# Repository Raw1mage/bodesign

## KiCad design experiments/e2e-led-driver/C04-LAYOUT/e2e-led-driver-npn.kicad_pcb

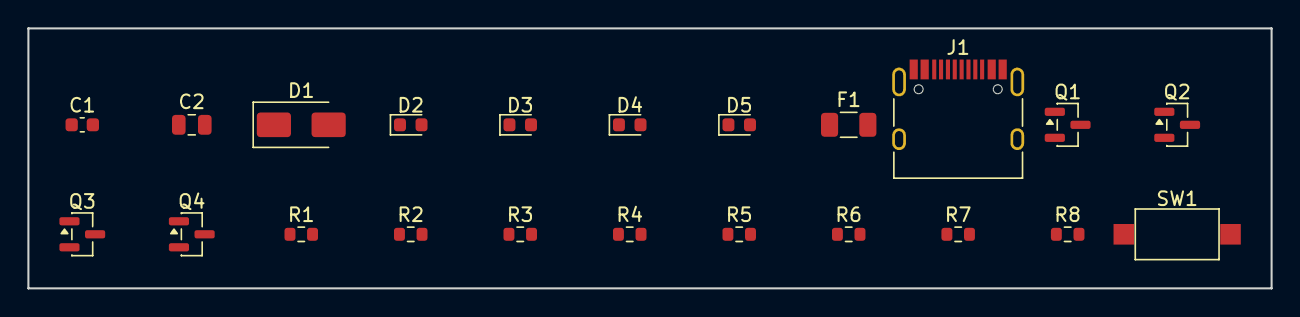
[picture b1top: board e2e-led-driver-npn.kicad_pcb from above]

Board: 2 copper layers, 90.8 x 19.0 mm, 22 parts (0 on the bottom side), 15 nets, no tracks yet.

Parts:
C1: C_0603_1608Metric
C2: C_0805_2012Metric
D1: D_SMA
D2, D3, D4, D5: LED_0603_1608Metric
F1: Fuse_1206_3216Metric
J1: USB_C_Receptacle_HRO_TYPE-C-31-M-12
Q1, Q2, Q3, Q4: SOT-23
R1, R2, R3, R4, R5, R6, R7, R8: R_0603_1608Metric
SW1: SW_SPST_CK_RS282G05A3

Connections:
CC1: J1.A5, R1.1
CC2: J1.B5, R2.1
GND: C1.2, C2.2, D1.2, J1.A1, J1.A12, J1.B1, J1.B12, R1.2, R2.2, R3.2, R4.2, R5.2, R6.2, R8.2
LED1_C: D2.1, Q1.2
LED2_C: D3.1, Q2.2
LED3_C: D4.1, Q3.2
LED4_C: D5.1, Q4.2
Q1_E: Q1.3, R3.1
Q2_E: Q2.3, R4.1
Q3_E: Q3.3, R5.1
Q4_E: Q4.3, R6.1
VBIAS: Q1.1, Q2.1, Q3.1, Q4.1, R7.2, R8.1
VBUS: D1.1, F1.1, J1.A4, J1.A9, J1.B4, J1.B9
VBUS_F: F1.2, SW1.1
VBUS_SW: C1.1, C2.1, D2.2, D3.2, D4.2, D5.2, R7.1, SW1.2

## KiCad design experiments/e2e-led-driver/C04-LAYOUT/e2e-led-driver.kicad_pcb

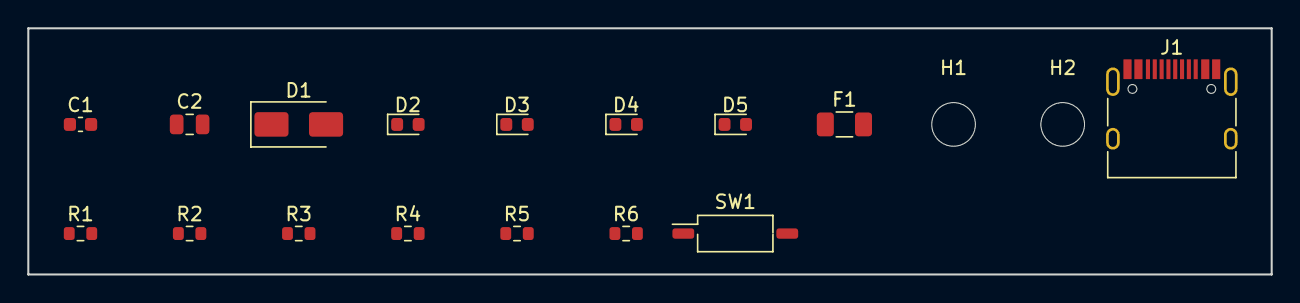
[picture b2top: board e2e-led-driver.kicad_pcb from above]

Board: 2 copper layers, 91.1 x 18.0 mm, 18 parts (0 on the bottom side), 10 nets, no tracks yet.

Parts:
C1: C_0603_1608Metric
C2: C_0805_2012Metric
D1: D_SMA
D2, D3, D4, D5: LED_0603_1608Metric
F1: Fuse_1206_3216Metric
H1, H2: MountingHole_3.2mm_M3
J1: USB_C_Receptacle_HRO_TYPE-C-31-M-12
R1, R2, R3, R4, R5, R6: R_0603_1608Metric
SW1: SW_DIP_SPSTx01_Slide_Copal_CHS-01B_W7.62mm_P1.27mm

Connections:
CC1: J1.A5, R1.1
CC2: J1.B5, R2.1
GND: C1.2, C2.2, D1.2, J1.A1, J1.A12, J1.B1, J1.B12, R1.2, R2.2, R3.2, R4.2, R5.2, R6.2
LED1_K: D2.1, R3.1
LED2_K: D3.1, R4.1
LED3_K: D4.1, R5.1
LED4_K: D5.1, R6.1
VBUS: D1.1, F1.1, J1.A4, J1.A9, J1.B4, J1.B9
VBUS_F: F1.2, SW1.1
VBUS_SW: C1.1, C2.1, D2.2, D3.2, D4.2, D5.2, SW1.2

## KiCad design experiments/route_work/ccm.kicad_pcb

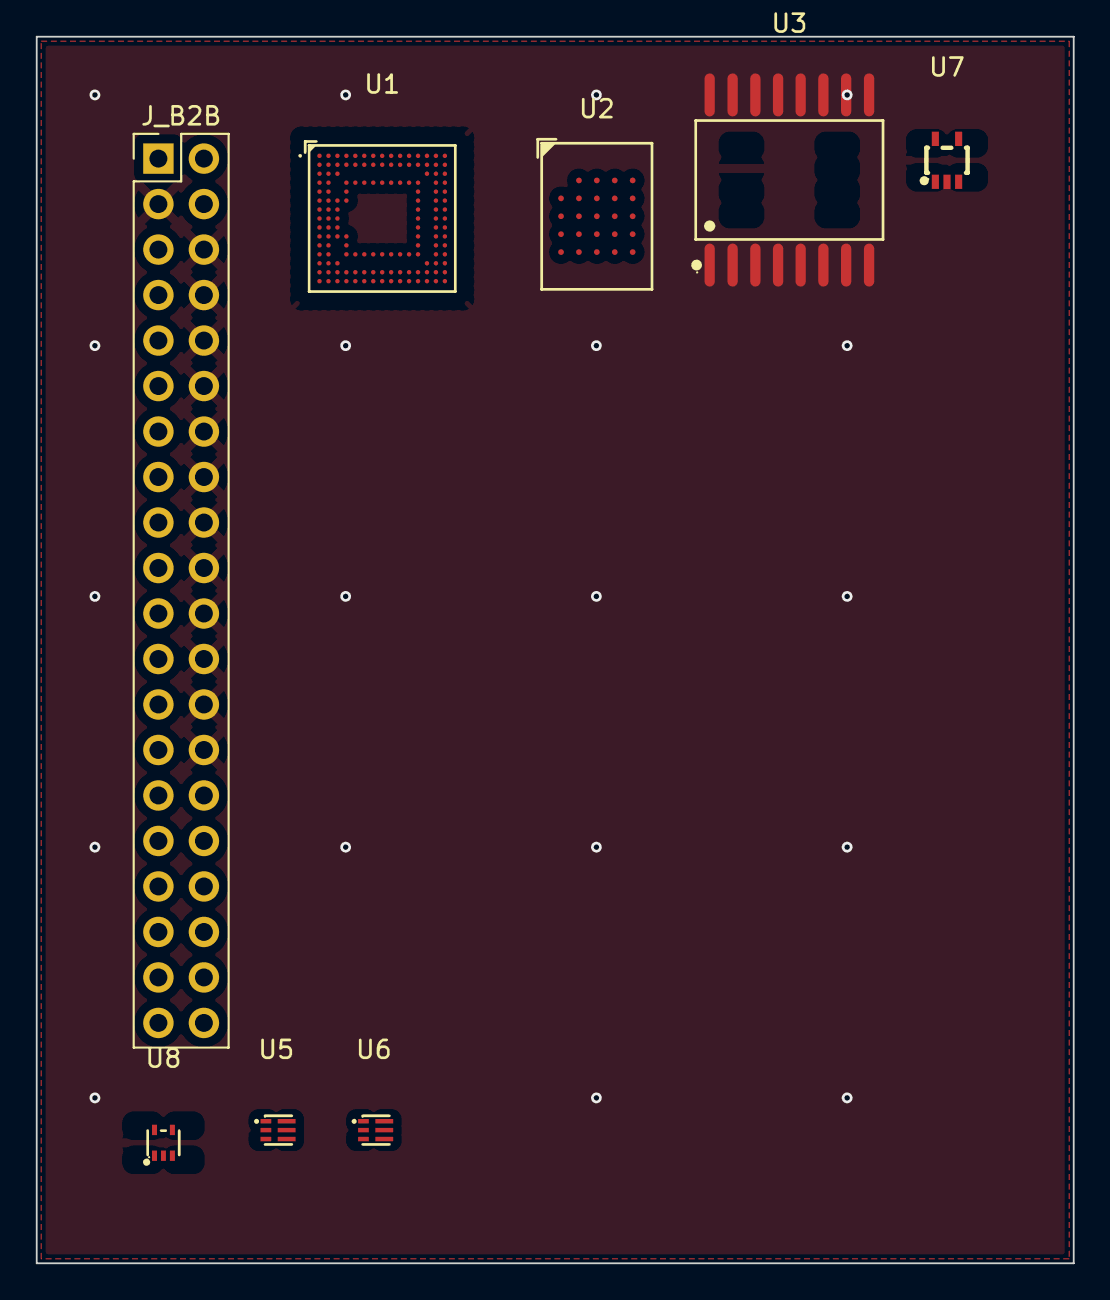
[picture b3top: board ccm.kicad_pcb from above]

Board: 4 copper layers, 57.9 x 68.5 mm, 8 parts (0 on the bottom side), 13 nets, no tracks yet.

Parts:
J_B2B: CCM-ECB B2B (visual stand-in, MPN open); PinHeader_2x20_P2.54mm_Vertical
U1: STM32N657L0; BGA-142_L8.0-W8.0-P0.50-TL_STM32N657Z0H3Q
U2: PSRAM 64MB xSPI2 (block); T-PBGA-24_L8.0-W6.0-P1.00-TL_MICRON_12
U3: Octal NOR Flash (block); SOIC-16_L10.3-W7.5-P1.27-LS10.3-BL
U5: TPS62826 3V3 buck; VSON-6_L1.5-W1.5-P0.50-TL
U6: TPS62824 1V8 buck; VSON-6_L1.5-W1.5-P0.50-TL
U7: MIC5365 VDDA LDO; SOT-323-5_L2.1-W1.3-P0.65-LS2.1-BL
U8: TCR2LE33 backup LDO; SOT-553-5_L1.6-W1.2-P0.50-LS1.6-BL

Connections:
+1V8: U1.J14, U1.K14, U1.L14, U2.A3, U3.4, U6.4
+3V3: J_B2B.4, J_B2B.5, U1.M14, U2.A2, U3.8, U5.4
BOOT0: J_B2B.15, U1.F4
GND: J_B2B.3, J_B2B.6, J_B2B.8, J_B2B.10, J_B2B.12, J_B2B.14, J_B2B.16, J_B2B.18, J_B2B.20, J_B2B.22, J_B2B.24, J_B2B.26, J_B2B.28, U1.F12, U1.H2, U1.H14, U1.J1, U1.J2, U1.J3, U1.P8, U1.P12, U1.P14, U3.2, U5.2, U6.2, U7.2, U8.2
NRST: J_B2B.13, U1.F2
SYS: J_B2B.1, J_B2B.2, U5.1, U6.1, U7.1, U8.1
USB_CC1: J_B2B.11, U1.A4
USB_DM: J_B2B.9, U1.B3
USB_DP: J_B2B.7, U1.A3
VDDA: U1.D4, U1.H1, U1.M6, U1.P6
VDDCORE: U1.P7, U1.P9, U1.P10, U1.P11, U1.P13
VDDSMPS: U1.L1, U1.L2, U1.L4
VLX: U1.K1, U1.K2, U1.K3, U1.K4
